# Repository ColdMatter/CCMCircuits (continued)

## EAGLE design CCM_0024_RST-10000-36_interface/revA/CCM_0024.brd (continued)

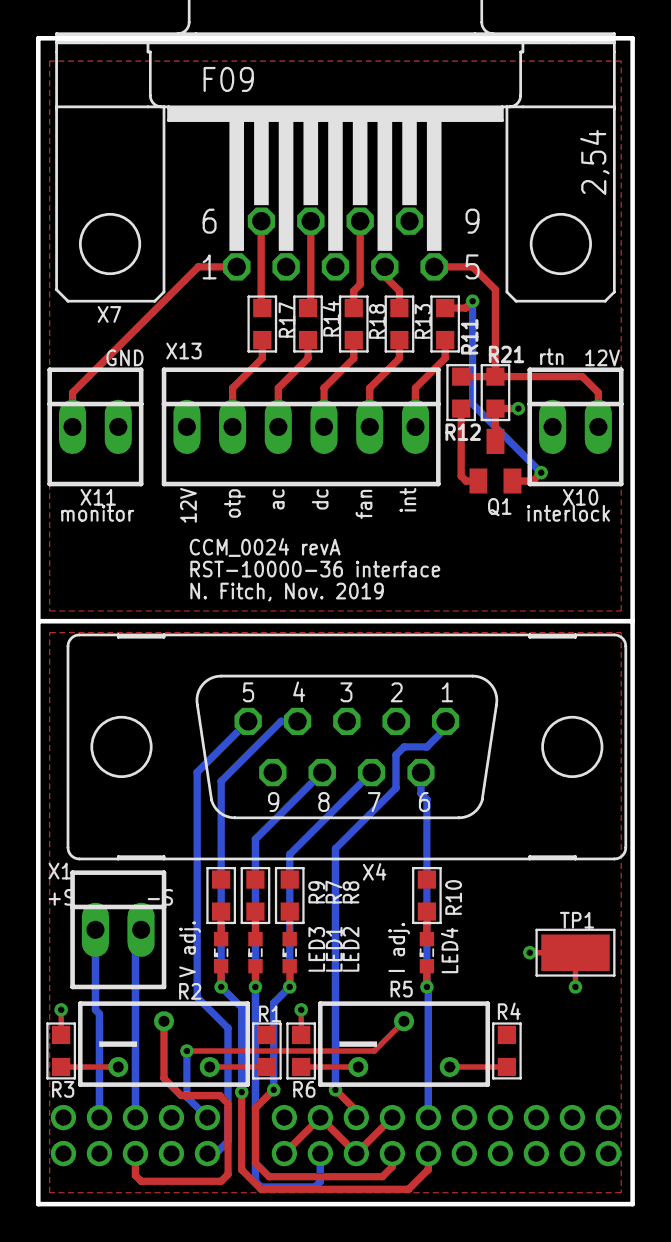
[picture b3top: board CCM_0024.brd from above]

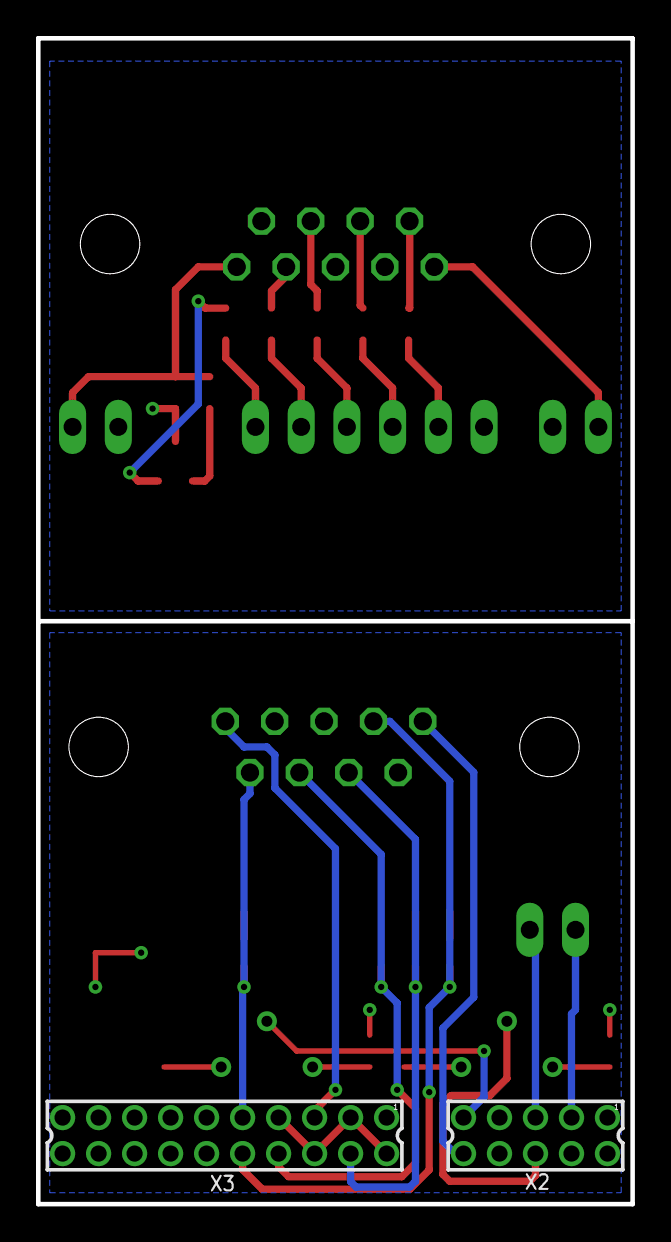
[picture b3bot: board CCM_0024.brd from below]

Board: 2 copper layers, 33.0 x 64.8 mm, 31 parts (2 on the bottom side), 35 nets.

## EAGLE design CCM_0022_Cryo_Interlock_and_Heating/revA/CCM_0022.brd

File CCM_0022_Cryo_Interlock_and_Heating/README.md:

Cryocooler Interlock and Heating
===========

This circuit acts as a control interface and safety interlock for the F50 cryocooler compressor and system heaters for our usual buffer-gas beam configuration of three heater channels.  Both manual or remote control options are available.  The circuit only allows the compressor to be activated if the external (NC) interlock is satisfied.  The initial build of the YbF "box" chamber uses hardware interlocks (in series) on the chamber pressure and temperature of the first and second cooler stages.  Heater control is completely independent of the interlock.  Activation of either the first or second stage (but not the SF6) heaters will disable the cryocooler.

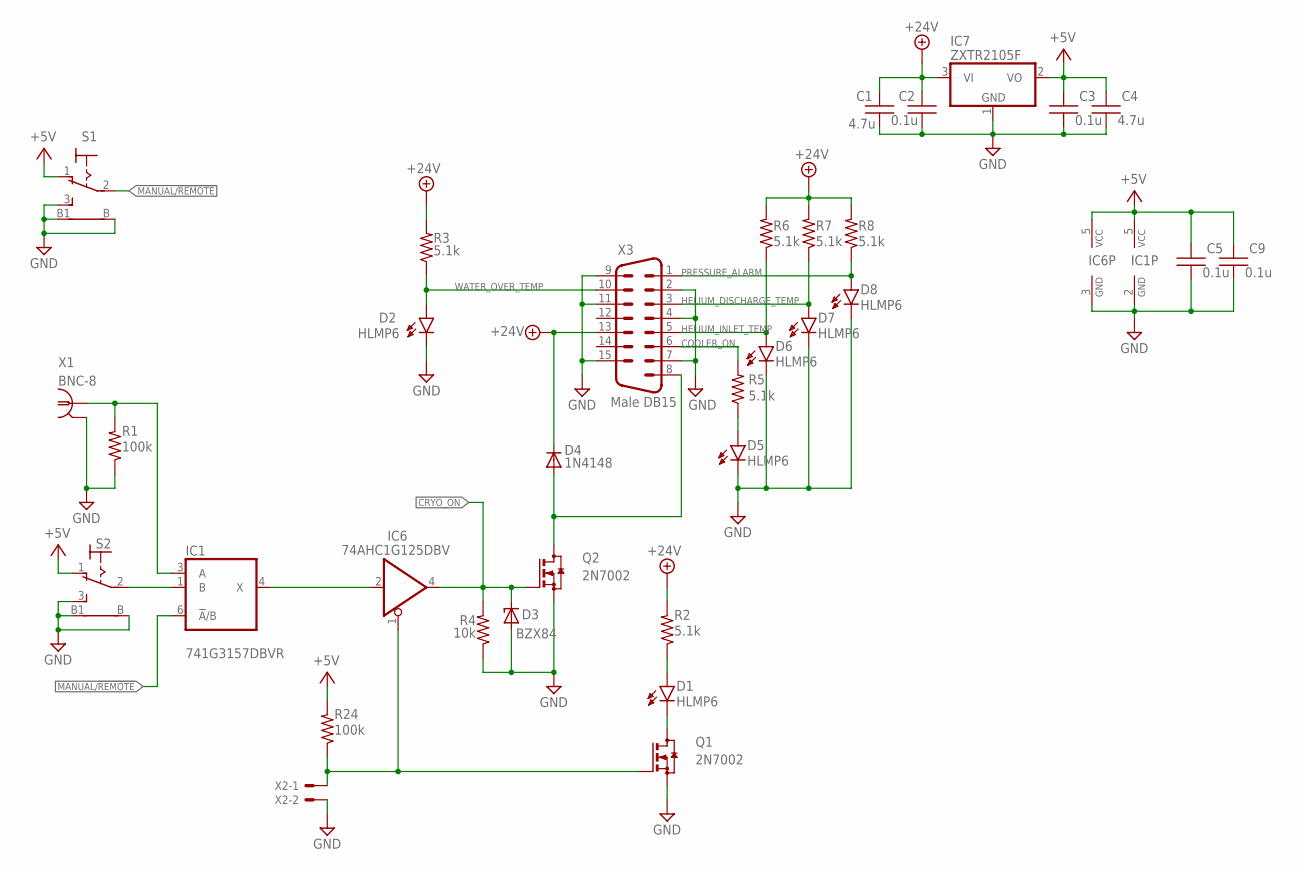
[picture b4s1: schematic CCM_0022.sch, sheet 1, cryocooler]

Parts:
C1, C4: 4.7u; 0603
C2, C3, C5, C9: 0.1u; 0603
D1, D2, D5, D6, D7, D8: HLMP6
D3: BZX84; TO236
D4: 1N4148; SOD323-W
IC1: 741G3157DBVR; DBV_R-PDSO-G6
IC6: 74AHC1G125DBV; SOT23-5
IC7: ZXTR2105F; SOT23
Q1, Q2: 2N7002; SOT23
R1, R24: 100k; 0603
R2, R3, R5, R6, R7, R8: 5.1k; 0603
R4: 10k; 0603
S1, S2: LPV-1
X1: BNC-8; BNC_RA
X2: 22-23-2021
X3: Male DB15; M15HP

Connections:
+5V: C3.1, C4.1, C5.1, C9.1, IC1.5 (VCC), IC6.5 (VCC), IC7.2 (VO), R24.2, S1.1 (O), S2.1 (O); also elsewhere on the board
+24V: C1.1, C2.1, D4.C, IC7.3 (VI), R2.2, R3.2, R6.2, R7.2, R8.2, X3.13
COOLER_ON: R5.2, X3.6
CRYO_ON: D3.C, IC6.4 (O), Q2.1 (G), R4.2; also elsewhere on the board
GND: C1.2, C2.2, C3.2, C4.2, C5.2, C9.2, D2.K, D3.A, D5.K, D6.K, D7.K, D8.K, IC1.2 (GND), IC6.3 (GND), IC7.1 (GND), Q1.2 (S), Q2.2 (S), R1.1, R4.1, S1.3 (S), S1.B, S1.B1, S2.3 (S), S2.B, S2.B1, X1.2, X2.2, X3.2, X3.4, X3.7, X3.9, X3.11, X3.15; also elsewhere on the board
HELIUM_DISCHARGE_TEMP: D7.A, R7.1, X3.3
HELIUM_INLET_TEMP: D6.A, R6.1, X3.5
MANUAL/!REMOTE: IC1.6 (!A!/B), S1.2; also elsewhere on the board
unnamed: D1.A, R2.1
unnamed: IC6.1 (OE), Q1.1 (G), R24.1, X2.1
unnamed: D1.K, Q1.3 (D)
unnamed: IC1.4 (X), IC6.2 (I)
unnamed: D5.A, R5.1
unnamed: D4.A, Q2.3 (D), X3.8
unnamed: IC1.3 (A), R1.2, X1.1
unnamed: IC1.1 (B), S2.2
PRESSURE_ALARM: D8.A, R8.1, X3.1
WATER_OVER_TEMP: D2.A, R3.1, X3.10

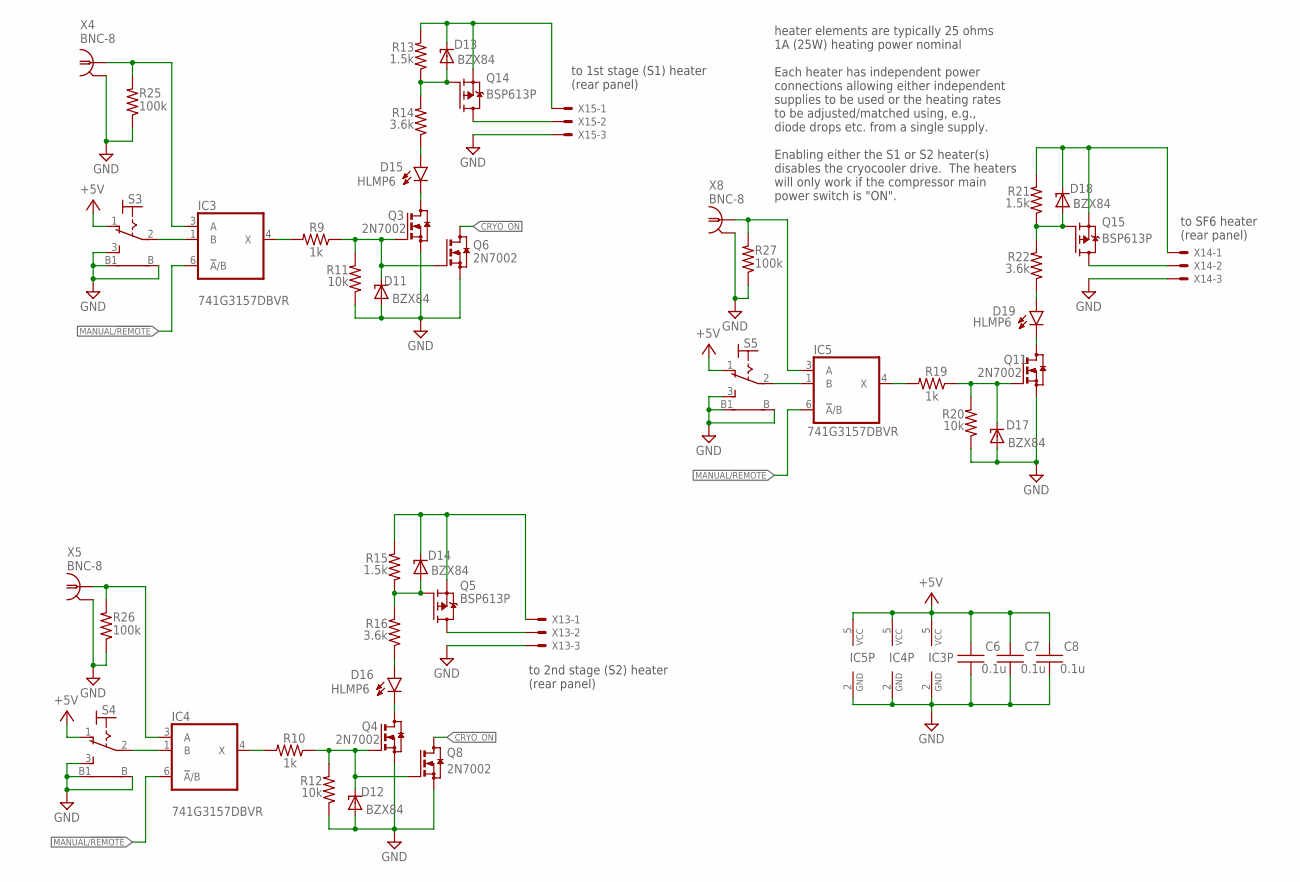
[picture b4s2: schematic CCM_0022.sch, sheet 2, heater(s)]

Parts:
C6, C7, C8: 0.1u; 0603
D11, D12, D13, D14, D17, D18: BZX84; TO236
D15, D16, D19: HLMP6
IC3, IC4, IC5: 741G3157DBVR; DBV_R-PDSO-G6
Q3, Q4, Q6, Q8, Q11: 2N7002; SOT23
Q5, Q14, Q15: BSP613P; SOT223
R9, R10, R19: 1k; 0603
R11, R12, R20: 10k; 0603
R13, R15, R21: 1.5k; 0603
R14, R16, R22: 3.6k; 0603
R25, R26, R27: 100k; 0603
S3, S4, S5: LPV-1
X4, X5, X8: BNC-8; BNC_RA
X13, X14, X15: 22-23-2031

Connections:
+5V: C6.1, C7.1, C8.1, IC3.5 (VCC), IC4.5 (VCC), IC5.5 (VCC), S3.1 (O), S4.1 (O), S5.1 (O); also elsewhere on the board
CRYO_ON: Q6.3 (D), Q8.3 (D); also elsewhere on the board
GND: C6.2, C7.2, C8.2, D11.A, D12.A, D17.A, IC3.2 (GND), IC4.2 (GND), IC5.2 (GND), Q3.2 (S), Q4.2 (S), Q6.2 (S), Q8.2 (S), Q11.2 (S), R11.1, R12.1, R20.1, R25.1, R26.1, R27.1, S3.3 (S), S3.B, S3.B1, S4.3 (S), S4.B, S4.B1, S5.3 (S), S5.B, S5.B1, X4.2, X5.2, X8.2, X13.3, X14.3, X15.3; also elsewhere on the board
MANUAL/!REMOTE: IC3.6 (!A!/B), IC4.6 (!A!/B), IC5.6 (!A!/B); also elsewhere on the board
unnamed: D13.C, Q14.3 (S), R13.2, X15.1
unnamed: D14.C, Q5.3 (S), R15.2, X13.1
unnamed: D16.A, R16.1
unnamed: D16.K, Q4.3 (D)
unnamed: D19.K, Q11.3 (D)
unnamed: D19.A, R22.1
unnamed: D15.K, Q3.3 (D)
unnamed: D15.A, R14.1
unnamed: D11.C, Q3.1 (G), Q6.1 (G), R9.1, R11.2
unnamed: D13.A, Q14.1 (G), R13.1, R14.2
unnamed: Q14.2 (D), Q14.4 (D), X15.2
unnamed: D12.C, Q4.1 (G), Q8.1 (G), R10.1, R12.2
unnamed: D14.A, Q5.1 (G), R15.1, R16.2
unnamed: Q5.2 (D), Q5.4 (D), X13.2
unnamed: IC4.3 (A), R26.2, X5.1
unnamed: IC4.1 (B), S4.2
unnamed: D17.C, Q11.1 (G), R19.1, R20.2
unnamed: D18.A, Q15.1 (G), R21.1, R22.2
unnamed: Q15.2 (D), Q15.4 (D), X14.2
unnamed: IC3.3 (A), R25.2, X4.1
unnamed: IC3.1 (B), S3.2
unnamed: IC5.3 (A), R27.2, X8.1
unnamed: IC5.1 (B), S5.2
S1_HEATER_ON/!OFF: IC3.4 (X), R9.2
S1_HEATER_ON/!OFF1: IC4.4 (X), R10.2
S1_HEATER_ON/!OFF2: IC5.4 (X), R19.2
SF6_HEATER_VOLTAGE: D18.C, Q15.3 (S), R21.2, X14.1

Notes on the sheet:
to 1st stage (S1) heater (rear panel)
heater elements are typically 25 ohms 1A (25W) heating power nominal Each heater has independent power connections allowing either independent supplies to be used or the heating rates to be adjusted/matched using, e.g., diode drops etc. from a single supply. Enabling either the S1 or S2 heater(s) d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
to 2nd stage (S2) heater (rear panel)
to SF6 heater (rear panel)

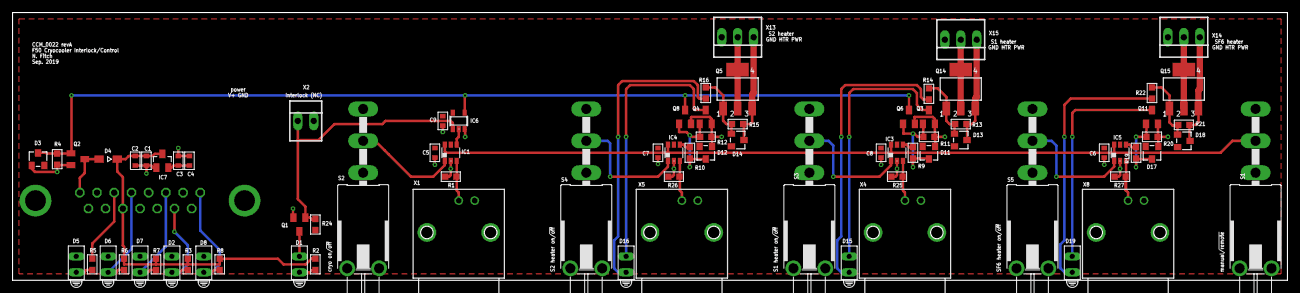
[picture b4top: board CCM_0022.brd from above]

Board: 2 copper layers, 203.2 x 42.7 mm, 80 parts (1 on the bottom side), 45 nets.

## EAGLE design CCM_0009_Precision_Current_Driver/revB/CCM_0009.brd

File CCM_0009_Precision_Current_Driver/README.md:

# Precision Current Driver
     
This is a low-noise, low-current, bipolar-capable precision current supply.  Revision B onwards is modeled after Analog Devices application note AN-968.  Populate components as necessary to produce unipolar/bipolar operation with the desired input voltage to current scaling.

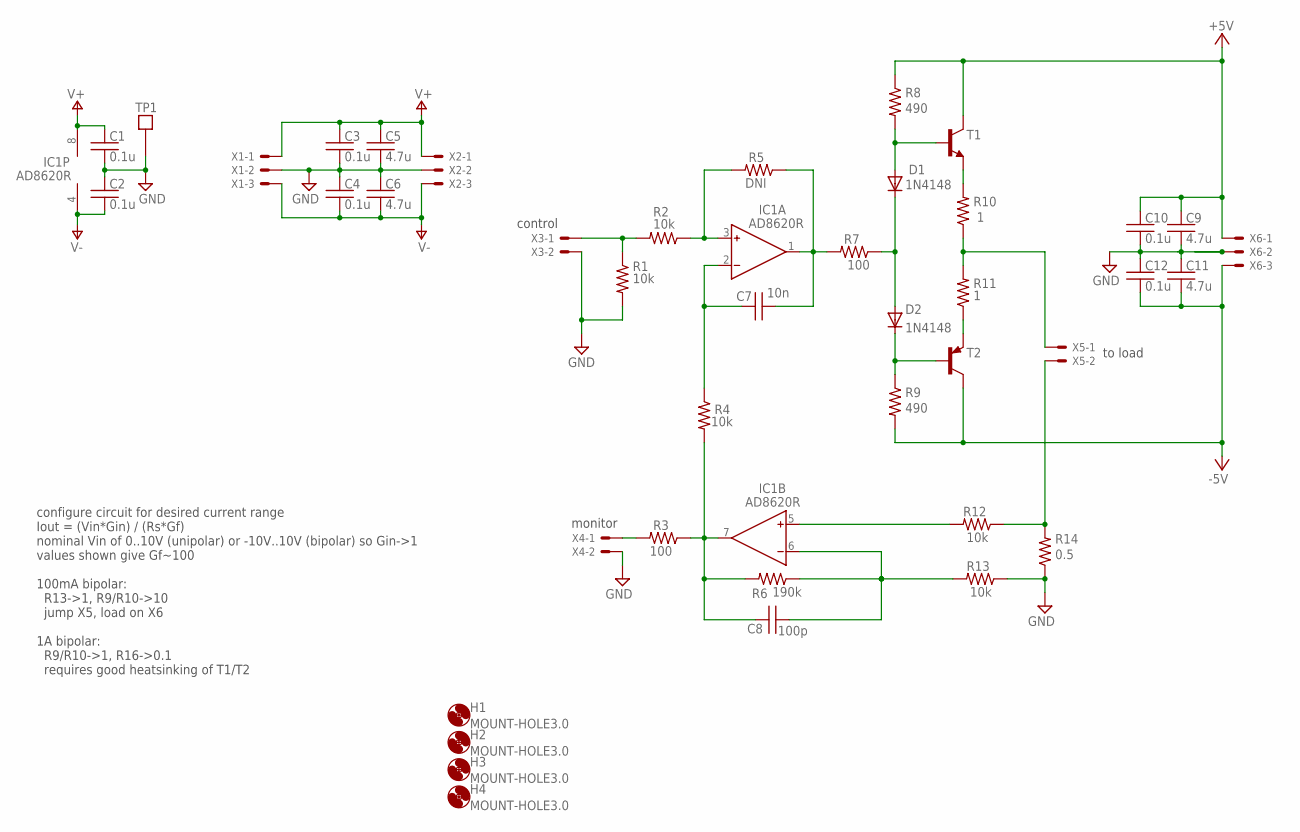
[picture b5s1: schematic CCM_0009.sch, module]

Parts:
C1, C2, C3, C4, C10, C12: 0.1u; 0603
C5, C6, C9, C11: 4.7u; 0603
C7: 10n; 0603
C8: 100p; 0603
D1, D2: 1N4148; SOD323_ST
H1, H2, H3, H4: MOUNT-HOLE3.0; 3,0
IC1: AD8620R; SO8
R1, R2, R4, R12, R13: 10k; 0603
R3, R7: 100; 0603
R5: DNI; 0603
R6: 190k; 0603
R8, R9: 490; 0603
R10, R11: 1; LTO30
R14: 0.5; LTO30
T1: TIP29; TO220V
T2: TIP30; TO220V
TP1: TESTPOINT
X1, X2, X6: 22-23-2031
X3, X4, X5: 22-23-2021

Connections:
+5V: C9.1, C10.1, R8.1, T1.2 (C), X6.1
-5V: C11.2, C12.2, R9.2, T2.2 (C), X6.3
B: R12.1, R14.P$2 (2), X5.2
GND: C1.2, C2.1, C3.2, C4.1, C5.2, C6.1, C9.2, C10.2, C11.1, C12.1, R1.2, R13.1, R14.P$1 (1), TP1.P$1, X1.2, X2.2, X3.2, X4.2, X6.2
unnamed: R11.P$1 (1), T2.3 (E)
unnamed: R10.P$1 (1), R11.P$2 (2), X5.1
unnamed: R10.P$2 (2), T1.3 (E)
unnamed: C7.2, IC1.1 (OUT), R5.1, R7.2
unnamed: IC1.5 (IN+), R12.2
unnamed: C8.2, IC1.6 (IN-), R6.1, R13.2
unnamed: D1.A, R8.2, T1.1 (B)
unnamed: R3.2, X4.1
unnamed: C8.1, IC1.7 (OUT), R3.1, R4.2, R6.2
unnamed: D1.C, D2.A, R7.1
unnamed: C7.1, IC1.2 (IN-), R4.1
unnamed: IC1.3 (IN+), R2.1, R5.2
unnamed: D2.C, R9.1, T2.1 (B)
unnamed: R1.1, R2.2, X3.1
V+: C1.1, C3.1, C5.1, IC1.8 (V+), X1.1, X2.1
V-: C2.2, C4.2, C6.2, IC1.4 (V-), X1.3, X2.3

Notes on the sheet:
control
configure circuit for desired current range Iout = (Vin*Gin) / (Rs*Gf) nominal Vin of 0..10V (unipolar) or -10V..10V (bipolar) so Gin->1 values shown give Gf~100 100mA bipolar: R13->1, R9/R10->10 jump X5, load on X6 1A bipolar: R9/R10->1, R16->0.1 requires good heatsinking of T1/T2
monitor
to load

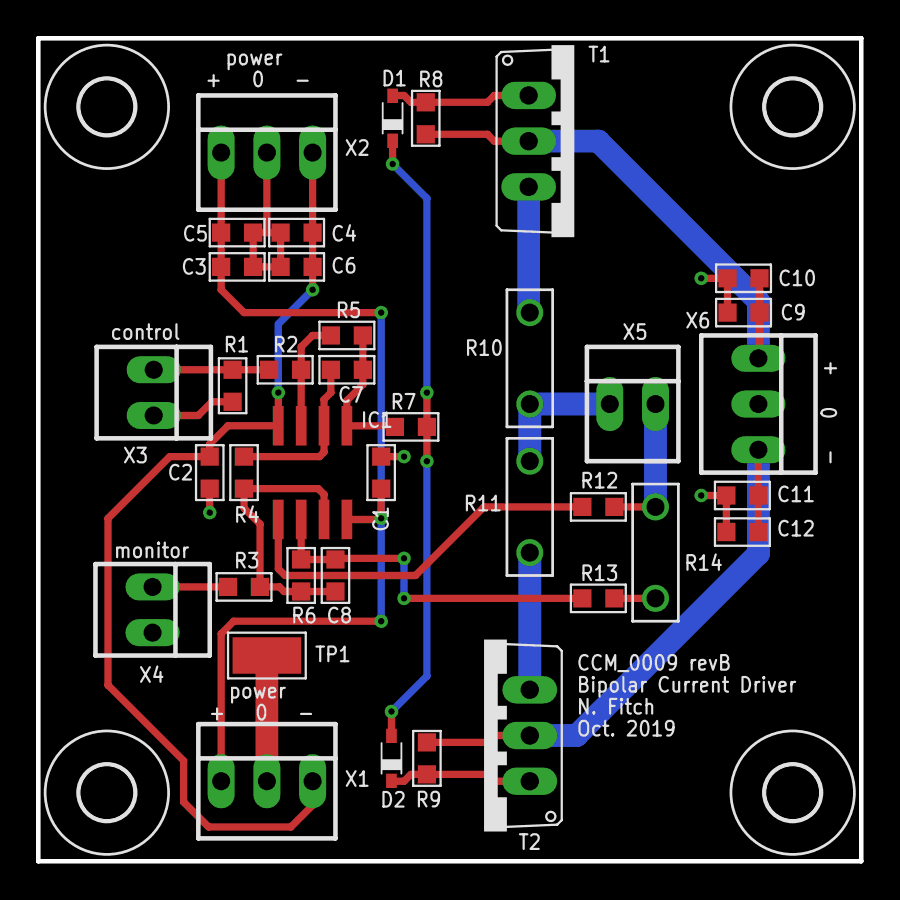
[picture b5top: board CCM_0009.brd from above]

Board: 2 copper layers, 45.7 x 45.7 mm, 42 parts (0 on the bottom side), 20 nets.

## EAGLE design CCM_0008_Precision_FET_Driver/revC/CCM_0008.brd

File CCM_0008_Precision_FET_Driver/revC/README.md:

Precision FET Driver
===========

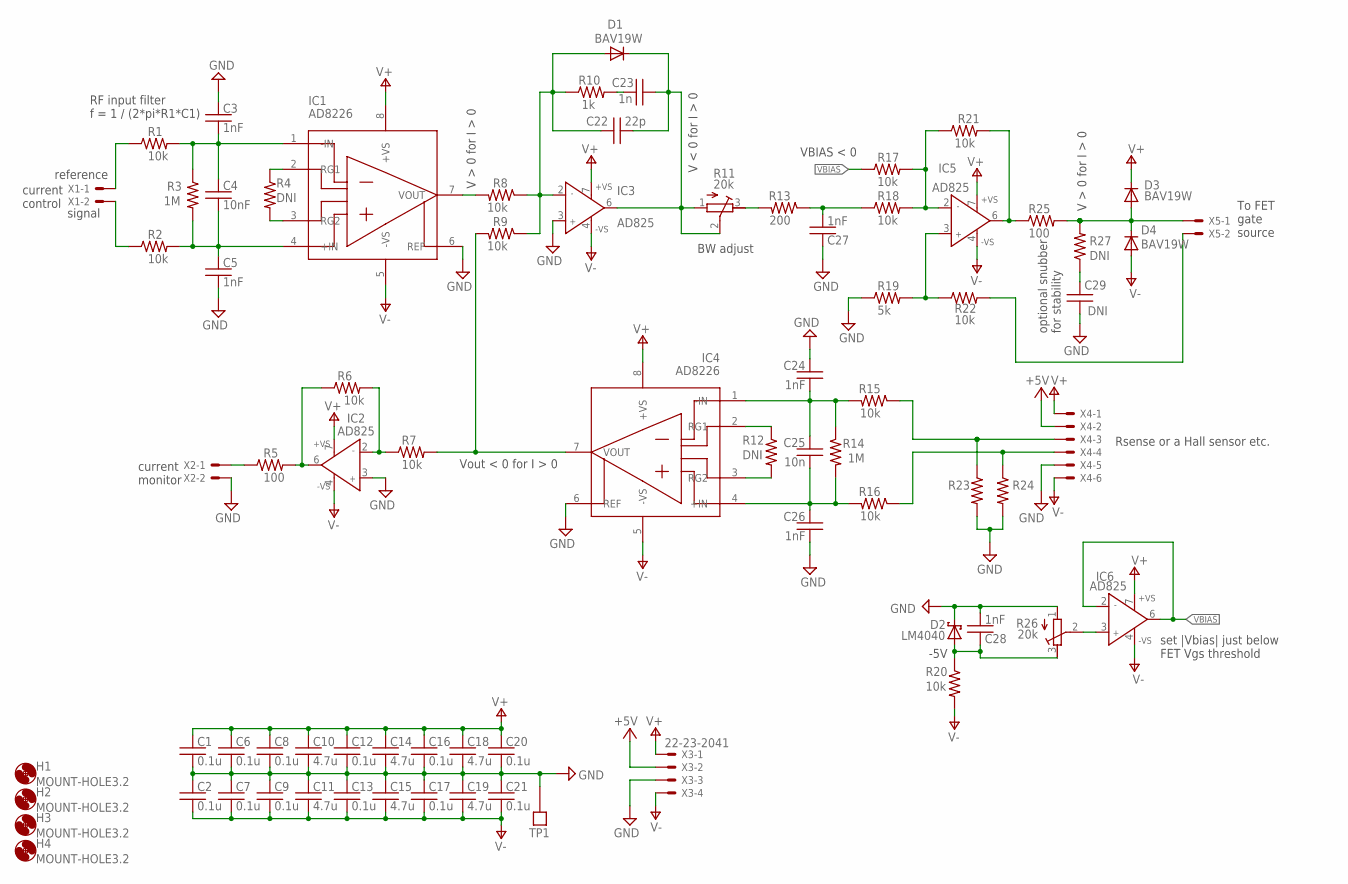
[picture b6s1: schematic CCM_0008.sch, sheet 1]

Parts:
C1, C2, C6, C7, C8, C9, C12, C13, C16, C17, C20, C21: 0.1u; 0603
C3, C5, C24, C26, C27, C28: 1nF; 0603
C4: 10nF; 0603
C10, C11, C14, C15, C18, C19: 4.7u; 0603
C22: 22p; 0603
C23: 1n; 0603
C25: 10n; 0603
C29: DNI; 0603
D1, D3, D4: BAV19W; SOD123
D2: LM4040; SOT23
H1, H2, H3, H4: MOUNT-HOLE3.2; 3,2
IC1, IC4: AD8226; SO08
IC2, IC3, IC5, IC6: AD825; SO8
R1, R2, R6, R7, R8, R9, R15, R16, R17, R18, R20, R21, R22: 10k; 0603
R3, R14: 1M; 0603
R4, R12, R27: DNI; 0603
R5, R25: 100; 0603
R10: 1k; 0603
R11, R26: 20k; RTRIM3224W
R13: 200; 0603
R19: 5k; 0603
R23, R24: ***; 0603
TP1: TESTPOINT
X1, X2, X5: 22-23-2021
X3: 22-23-2041
X4: 22-23-2061

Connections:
+5V: X3.2, X4.2
GND: C1.2, C2.1, C3.1, C5.2, C6.2, C7.1, C8.2, C9.1, C10.2, C11.1, C12.2, C13.1, C14.2, C15.1, C16.2, C17.1, C18.2, C19.1, C20.2, C21.1, C24.1, C26.2, C27.1, C28.2, C29.2, D2.1 (C), IC1.6 (REF), IC2.3 (IN+), IC3.3 (IN+), IC4.6 (REF), R19.1, R23.2, R24.2, R26.1 (A), TP1.P$1, X2.2, X3.3, X4.5
unnamed: R2.1, X1.2
unnamed: R1.1, X1.1
unnamed: C22.1, C23.1, D1.C, IC3.6 (OUT), R11.1 (A), R11.2 (S)
unnamed: IC1.2 (RG1), R4.1
unnamed: C3.2, C4.1, IC1.1 (-IN), R1.2, R3.1
unnamed: C4.2, C5.1, IC1.4 (+IN), R2.2, R3.2
unnamed: R5.1, X2.1
unnamed: IC1.3 (RG2), R4.2
unnamed: IC2.6 (OUT), R5.2, R6.1
unnamed: IC2.2 (IN-), R6.2, R7.1
unnamed: IC5.3 (IN+), R19.2, R22.1
unnamed: IC4.7 (VOUT), R7.2, R9.2
unnamed: C27.2, R13.1, R18.1
unnamed: IC5.2 (IN-), R17.2, R18.2, R21.1
unnamed: IC1.7 (VOUT), R8.2
unnamed: IC5.6 (OUT), R21.2, R25.1
unnamed: R11.3 (E), R13.2
unnamed: R22.2, X5.2
unnamed: D3.A, D4.C, R25.2, R27.2, X5.1
unnamed: C28.1, D2.2 (A), R20.1, R26.3 (E)
unnamed: R16.1, R24.1, X4.4
unnamed: IC6.3 (IN+), R26.2 (S)
unnamed: IC4.2 (RG1), R12.1
unnamed: IC4.3 (RG2), R12.2
unnamed: C24.2, C25.1, IC4.1 (-IN), R14.1, R15.2
unnamed: C25.2, C26.1, IC4.4 (+IN), R14.2, R16.2
unnamed: R15.1, R23.1, X4.3
unnamed: C29.1, R27.1
unnamed: C23.2, R10.2
unnamed: C22.2, D1.A, IC3.2 (IN-), R8.1, R9.1, R10.1
V+: C1.1, C6.1, C8.1, C10.1, C12.1, C14.1, C16.1, C18.1, C20.1, D3.C, IC1.8 (+VS), IC2.7 (+VS), IC3.7 (+VS), IC4.8 (+VS), IC5.7 (+VS), IC6.7 (+VS), X3.1, X4.1
V-: C2.2, C7.2, C9.2, C11.2, C13.2, C15.2, C17.2, C19.2, C21.2, D4.A, IC1.5 (-VS), IC2.4 (-VS), IC3.4 (-VS), IC4.5 (-VS), IC5.4 (-VS), IC6.4 (-VS), R20.2, X3.4, X4.6
VBIAS: IC6.2 (IN-), IC6.6 (OUT), R17.1

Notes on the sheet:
current control
RF input filter f = 1 / (2*pi*R1*C1)
optional snubber for stability
current monitor
signal
reference
To FET gate source
Rsense or a Hall sensor etc.
Vout < 0 for I > 0
BW adjust
-5V
V > 0 for I > 0
V < 0 for I > 0
set |Vbias| just below FET Vgs threshold
VBIAS < 0

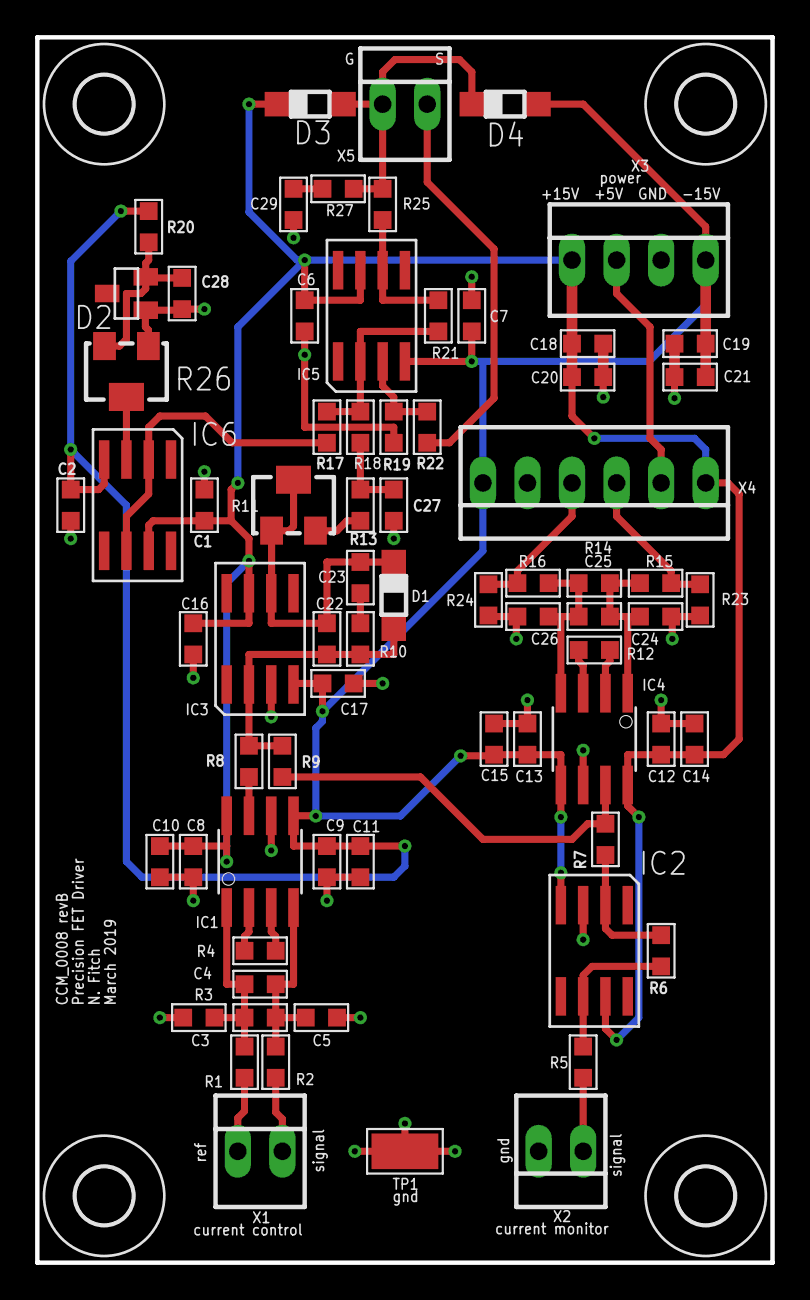
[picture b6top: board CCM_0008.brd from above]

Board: 2 copper layers, 41.9 x 69.8 mm, 76 parts (0 on the bottom side), 35 nets.

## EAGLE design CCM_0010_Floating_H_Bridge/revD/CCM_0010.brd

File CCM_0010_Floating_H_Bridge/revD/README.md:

# CCM 0010 RevD

This is revision D of the floating H-bridge + bypass circuit that we use to control our CaF MOT and transport coils.  The bypass circuit feedback/control should use circuit CCM_0008 or equivalent.  For the bypass circuit current sensing, any galvanically isolated current sensor can be used, but **do not** use a sense resistor.  The FET drive side is floating and will definitely break the lab-ground referenced feedback instrumentation amplifier on CCM_0008.

## RevD Changes
- The HIP4082 full h-bridge driver has been replaced by a HIP4081a.  The former drives the upper FET gates using (solely) a bootstrap supply that only recharges when switching the h-bridge.  We typically operate at or near 100% duty cycle so only very rarely switch the h-bridge.  This means that the bootstrap supply isn't operating properly, limiting the gate voltage available to drive the upper FET gates.  This is especially true when the voltage drop across the load approaches a few volts; the bootstrap supply is operating around 12V above local ground and combined with the load voltage drop limits the gate voltage available to the FET.  Using the IXFN360N FET at 150A, the voltage drop across the load (1/2 of the transport coils) is 8V, leaving only 4V for the FET gate-source voltage.  This means the FET is turning off when it should be conducting hard, meaning that the power dissipation is too high.  We've already lost one of the h-bridge FETs this way.  

## Known Issues

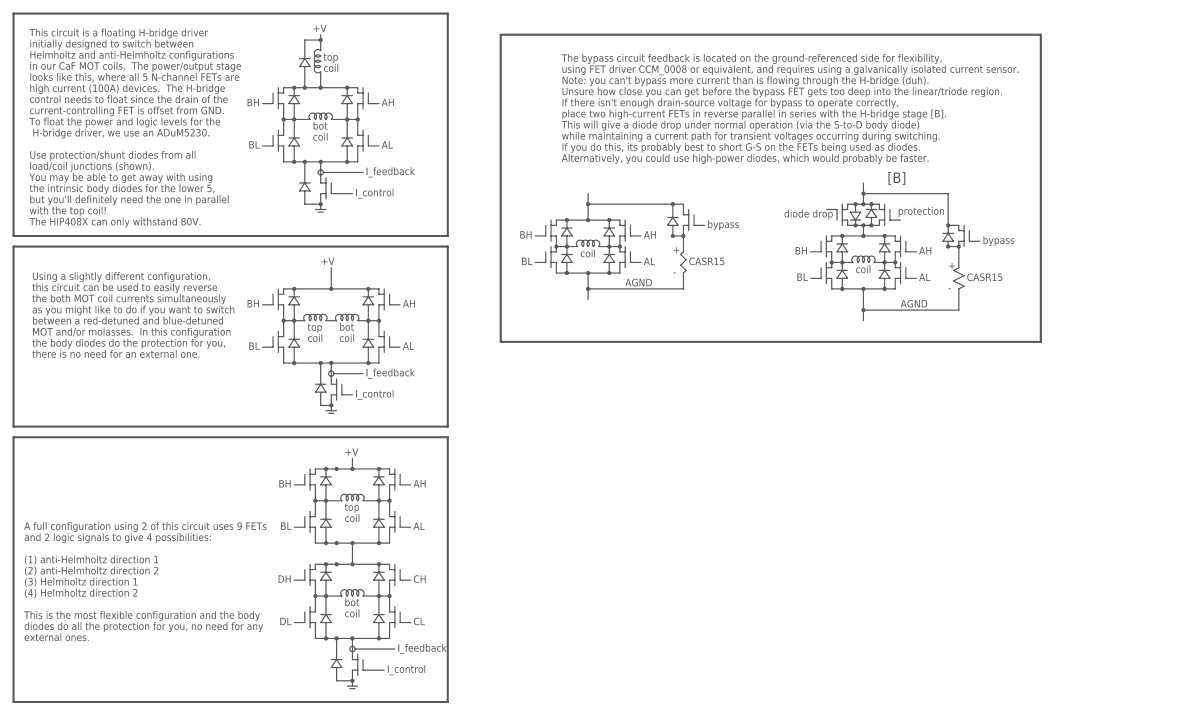
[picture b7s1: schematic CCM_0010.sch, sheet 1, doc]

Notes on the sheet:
I_control
top coil
bot coil
This circuit is a floating H-bridge driver initially designed to switch between Helmholtz and anti-Helmholtz configurations in our CaF MOT coils. The power/output stage looks like this, where all 5 N-channel FETs are high current (100A) devices. The H-bridge control needs to float since the drain o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
I_feedback
Using a slightly different configuration, this circuit can be used to easily reverse the both MOT coil currents simultaneously as you might like to do if you want to switch between a red-detuned and blue-detuned MOT and/or molasses. In this configuration the body diodes do the protection for you, t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
A full configuration using 2 of this circuit uses 9 FETs and 2 logic signals to give 4 possibilities: (1) anti-Helmholtz direction 1 (2) anti-Helmholtz direction 2 (3) Helmholtz direction 1 (4) Helmholtz direction 2 This is the most flexible configuration and the body diodes do all the protection f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
The bypass circuit feedback is located on the ground-referenced side for flexibility, using FET driver CCM_0008 or equivalent, and requires using a galvanically isolated current sensor. Note: you can't bypass more current than is flowing through the H-bridge (duh). Unsure how close you can get befo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
coil
bypass
CASR15
+ -
AGND
[B]
protection
diode drop

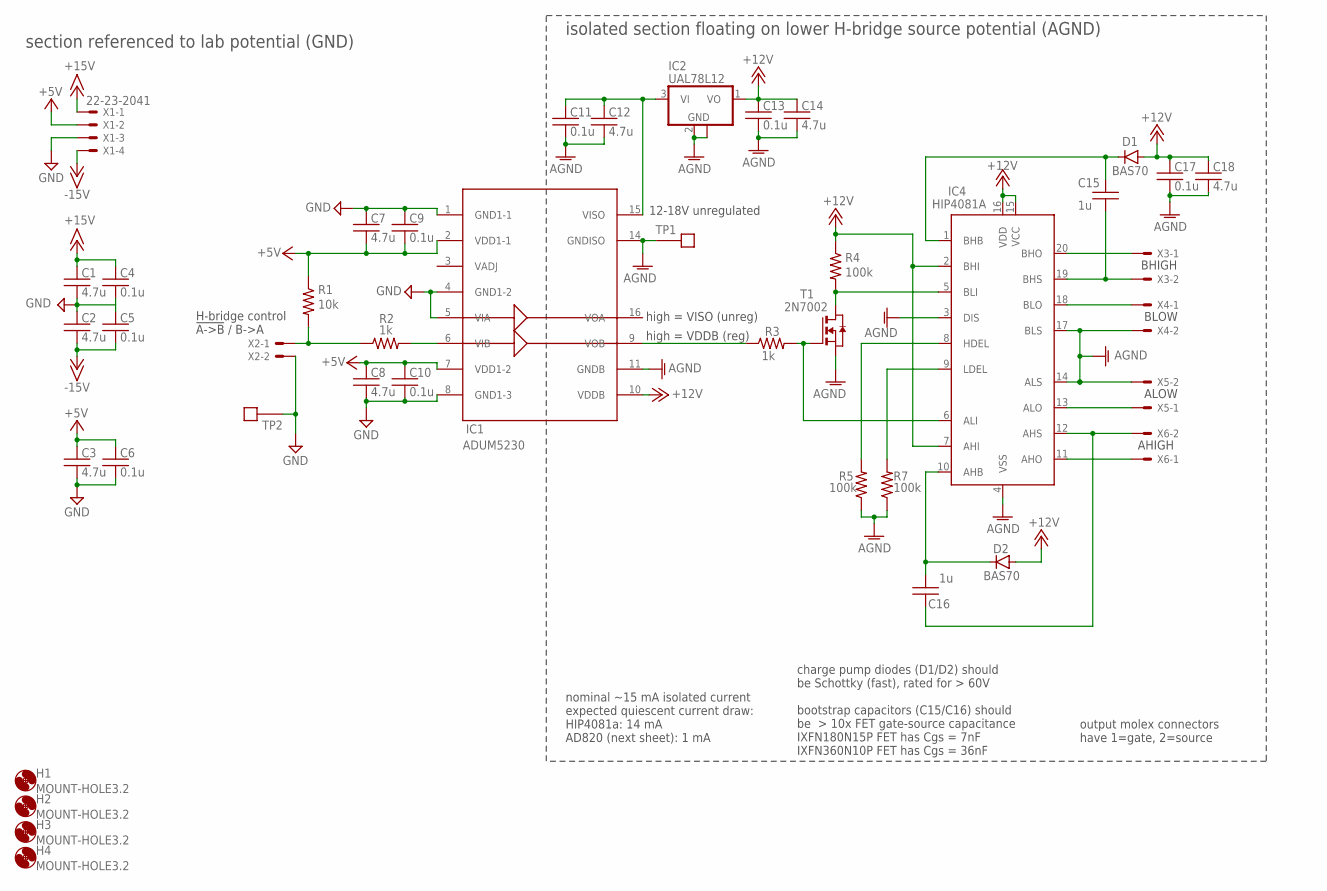
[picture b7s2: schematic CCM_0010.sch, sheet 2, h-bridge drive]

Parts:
C1, C2, C3, C7, C8, C12, C14, C18: 4.7u; 0603
C4, C5, C6, C9, C10, C11, C13, C17: 0.1u; 0603
C15, C16: 1u; 0603
D1, D2: BAS70; SOT23-3
H1, H2, H3, H4: MOUNT-HOLE3.2; 3,2
IC1: ADUM5230; SO16W
IC2: UAL78L12; SOT89
IC4: HIP4081A; SO20
R1: 10k; 0603
R2, R3: 1k; 0603
R4, R5, R7: 100k; 0603
T1: 2N7002; SOT-23
TP1, TP2: TESTPOINT
X1: 22-23-2041
X2, X3, X4, X5, X6: 22-23-2021

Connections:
+5V: C3.1, C6.1, C7.2, C8.1, C9.2, C10.1, IC1.2 (VDD1-1), IC1.7 (VDD1-2), R1.1, X1.2
+12V: C13.1, C14.1, C17.1, C18.1, D1.1 (A), D2.1 (A), IC1.10 (VDDB), IC2.1 (VO), IC4.2 (BHI), IC4.7 (AHI), IC4.15 (VCC), IC4.16 (VDD), R4.1; also elsewhere on the board
+15V: C1.1, C4.1, X1.1; also elsewhere on the board
-15V: C2.2, C5.2, X1.4; also elsewhere on the board
AGND: C11.2, C12.2, C13.2, C14.2, C17.2, C18.2, IC1.11 (GNDB), IC1.14 (GNDISO), IC2.2 (GND), IC2.2@1 (GND), IC4.3 (DIS), IC4.4 (VSS), IC4.14 (ALS), IC4.17 (BLS), R5.1, R7.1, T1.2 (S), TP1.P$1, X4.2, X5.2; also elsewhere on the board
GND: C1.2, C2.1, C3.2, C4.2, C5.1, C6.2, C7.1, C8.2, C9.1, C10.2, IC1.1 (GND1-1), IC1.4 (GND1-2), IC1.5 (VIA), IC1.8 (GND1-3), TP2.P$1, X1.3, X2.2; also elsewhere on the board
unnamed: IC4.18 (BLO), X4.1
unnamed: IC4.13 (ALO), X5.1
unnamed: IC4.8 (HDEL), R5.2
unnamed: C16.1, D2.3 (C), IC4.10 (AHB)
unnamed: C11.1, C12.1, IC1.15 (VISO), IC2.3 (VI)
unnamed: IC1.9 (VOB), R3.1
unnamed: C16.2, IC4.12 (AHS), X6.2
unnamed: C15.2, D1.3 (C), IC4.1 (BHB)
unnamed: IC4.9 (LDEL), R7.2
unnamed: IC4.5 (BLI), R4.2, T1.1 (D)
unnamed: IC4.6 (ALI), R3.2, T1.3 (G)
unnamed: C15.1, IC4.19 (BHS), X3.2
unnamed: IC4.20 (BHO), X3.1
unnamed: R1.2, R2.1, X2.1
unnamed: IC1.6 (VIB), R2.2
unnamed: IC4.11 (AHO), X6.1

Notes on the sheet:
H-bridge control !A->B! / B->A
12-18V unregulated
high = VISO (unreg)
high = VDDB (reg)
output molex connectors have 1=gate, 2=source
charge pump diodes (D1/D2) should be Schottky (fast), rated for > 60V bootstrap capacitors (C15/C16) should be > 10x FET gate-source capacitance IXFN180N15P FET has Cgs = 7nF IXFN360N10P FET has Cgs = 36nF
nominal ~15 mA isolated current expected quiescent current draw: HIP4081a: 14 mA AD820 (next sheet): 1 mA
BHIGH
BLOW
ALOW
AHIGH
isolated section floating on lower H-bridge source potential (AGND)
section referenced to lab potential (GND)

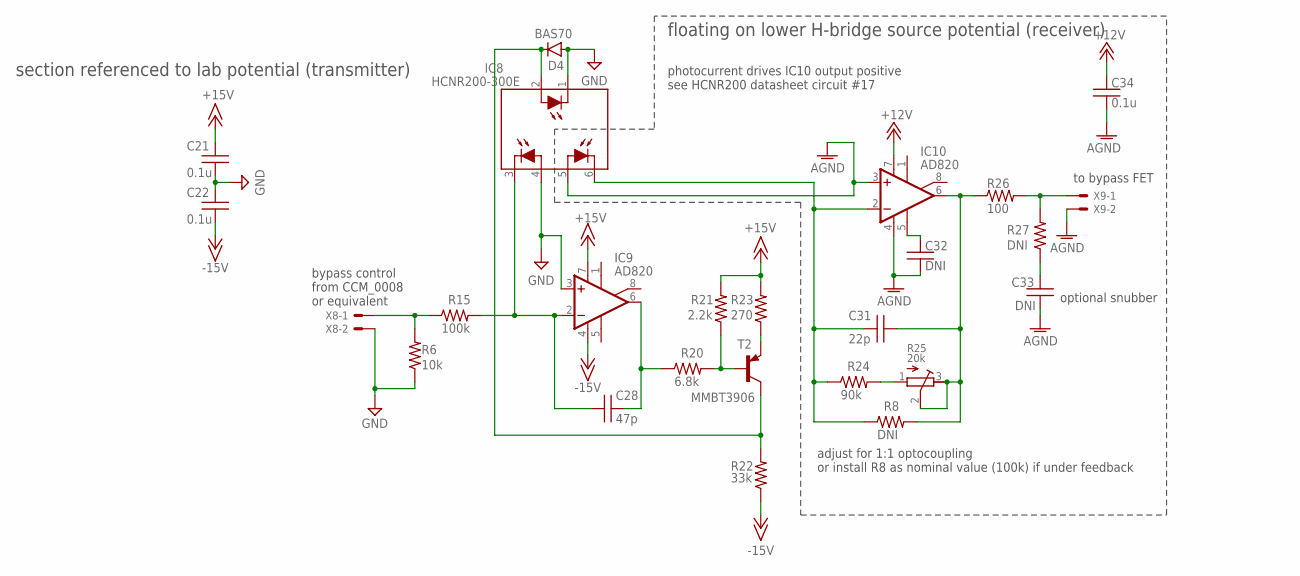
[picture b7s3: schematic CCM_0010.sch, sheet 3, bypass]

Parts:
C21, C22, C34: 0.1u; 0603
C28: 47p; 0603
C31: 22p; 0603
C32, C33: DNI; 0603
D4: BAS70; SOT23-3
IC8: HCNR200-300E; DIP8-400
IC9, IC10: AD820; SO08
R6: 10k; 0603
R8, R27: DNI; 0603
R15: 100k; 0603
R20: 6.8k; 0603
R21: 2.2k; 0603
R22: 33k; 0603
R23: 270; 0603
R24: 90k; 0603
R25: 20k; RTRIM3224W
R26: 100; 0603
T2: MMBT3906; SOT23-BEC
X8, X9: 22-23-2021

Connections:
+12V: C34.1, IC10.7 (V+); also elsewhere on the board
+15V: C21.2, IC9.7 (V+), R21.2, R23.2; also elsewhere on the board
-15V: C22.1, IC9.4 (V-), R22.1; also elsewhere on the board
AGND: C32.2, C33.2, C34.2, IC8.5 (A2), IC10.3 (+IN), IC10.4 (V-), X9.2; also elsewhere on the board
GND: C21.1, C22.2, D4.1 (A), IC8.1 (C), IC8.4 (A1), IC9.3 (+IN), R6.1, X8.2; also elsewhere on the board
unnamed: C32.1, IC10.5 (OPT)
unnamed: D4.3 (C), IC8.2 (A), R22.2, T2.C
unnamed: C33.1, R27.1
unnamed: R6.2, R15.1, X8.1
unnamed: C28.2, IC8.3 (C1), IC9.2 (-IN), R15.2
unnamed: R24.2, R25.1 (A)
unnamed: C28.1, IC9.6 (OUT), R20.1
unnamed: R20.2, R21.1, T2.B
unnamed: R23.1, T2.E
unnamed: C31.2, IC8.6 (C2), IC10.2 (-IN), R8.1, R24.1
unnamed: C31.1, IC10.6 (OUT), R8.2, R25.2 (S), R25.3 (E), R26.1
unnamed: R26.2, R27.2, X9.1

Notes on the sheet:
floating on lower H-bridge source potential (receiver)
section referenced to lab potential (transmitter)
adjust for 1:1 optocoupling or install R8 as nominal value (100k) if under feedback
to bypass FET
bypass control from CCM_0008 or equivalent
photocurrent drives IC10 output positive see HCNR200 datasheet circuit #17
optional snubber

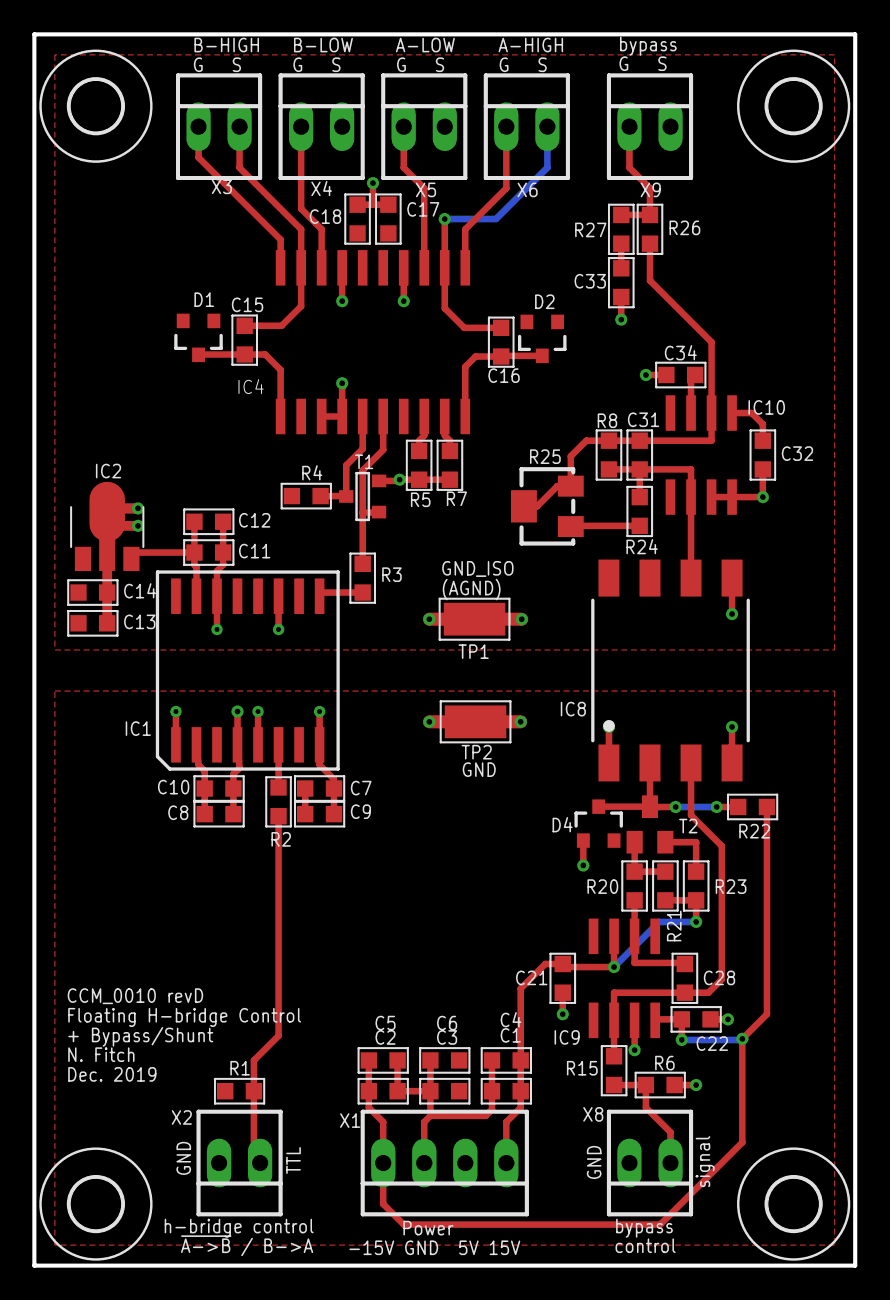
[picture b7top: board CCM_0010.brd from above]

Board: 2 copper layers, 50.8 x 76.2 mm, 67 parts (0 on the bottom side), 34 nets.
